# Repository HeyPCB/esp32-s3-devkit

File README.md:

# ESP32-S3 DevKit

A 31 × 64 mm ESP32-S3 development board laid out like Espressif's DevKitC-1: the WROOM-1 module at the top with its antenna on the edge, an 18-pin header down each side, three WS2812B LEDs, and USB-C between RST and BOOT.

An agent built it through [HeyPCB's MCP server](https://heypcb.ai/mcp): blocks, parts, nets, hand placement, routing and checks, all as tool calls. KiCad 10 opens the files directly, and the board is on [Circuit World](https://heypcb.ai/world/b/a0fca22e9815) to open or fork in HeyPCB (sign-in required).

## What's on it

- **ESP32-S3-WROOM-1-N8R8** (8 MB flash, 8 MB octal PSRAM). IO35–IO37 go to the PSRAM, so they are not broken out.
- **USB-C** (HRO TYPE-C-31-M-12) wired to the chip's native USB on IO19/IO20, through a **USBLC6-2SC6** ESD array, with 5.1 kΩ pull-downs on CC1 and CC2.
- **AMS1117-3.3** regulator, 5 V from USB to 3.3 V.
- **Three WS2812B LEDs** chained from IO48 through a 330 Ω resistor, powered from 5 V through a 1N5819W Schottky.
- **RST** pulls EN low and **BOOT** pulls IO0 low, with 10 kΩ pull-ups to 3.3 V and 100 nF to ground.
- **4 layers** on JLCPCB's 4-layer rules. In1 is a solid ground plane; the other three layers carry signals with ground poured around them.

Every part has an LCSC number in the BOM.

## Pinout

Headers are 2.54 mm pitch, 27.94 mm (1.1 in) between rows. Pin 1 is at the antenna end on both sides.

| Pin | Left (J2) | Right (J3) |
|---:|---|---|
| 1 | 3V3 | GND |
| 2 | EN (reset) | IO1 |
| 3 | IO4 | IO2 |
| 4 | IO5 | TXD0 |
| 5 | IO6 | RXD0 |
| 6 | IO7 | IO42 |
| 7 | IO15 | IO41 |
| 8 | IO16 | IO40 |
| 9 | IO17 | IO39 |
| 10 | IO18 | IO38 |
| 11 | IO8 | IO0 (BOOT) |
| 12 | IO3 | IO45 |
| 13 | IO46 | IO48 (LED data) |
| 14 | IO9 | IO47 |
| 15 | IO10 | IO21 |
| 16 | IO11 | IO14 |
| 17 | IO12 | IO13 |
| 18 | 5V (USB VBUS) | GND |

## Checks

Measured on this revision:

| Check | Result |
|---|---|
| DRC, HeyPCB | 0 errors, 0 unconnected |
| DRC, KiCad 10.0.6 run locally | 0 errors, 0 unconnected |
| ERC | 0 errors |
| HeyPCB verify (DRC, ERC, artwork copper, electrical rules, simulation, IR drop, physical, DFM, placement, thermal) | all 10 pass |
| Fab readiness (JLCPCB) | ready to order, 14 checks passed |

Warnings the board still carries:

- **USB pair skew is 1.45 mm against a 1.25 mm rule.** USB_DP measures 47.73 mm and USB_DN 46.28 mm. The rule comes from the USB 2.0 preset; the ESP32-S3's USB is full speed (12 Mbps). The two lines run side by side on the bottom layer, but they are not a tightly coupled pair.
- VBUS can peak at 540 mA while HeyPCB budgets 500 mA for J1, so it suggests about 290 µF more bulk capacitance near the connector.
- The regulator's input and output capacitors sit 9–10 mm from its pins: inside the limit, flagged as marginal.
- The antenna reaches free space at the top edge, but HeyPCB notes the side edges, and their ground pour, run close beside it.
- The module's ground pad has no thermal vias.
- No fiducials. J1 is a JLCPCB Extended part (a $3 feeder fee).
- A few silkscreen clearance nits.

## Files

| Path | What it is |
|---|---|
| `esp32-s3-devkit.kicad_pro`, `.kicad_sch`, `.kicad_pcb` | The KiCad 10 project |
| `heypcb-libs/` | The one footprint not in KiCad's standard library (USBLC6-2SC6, SOT-23-6), wired up by `fp-lib-table` |
| `design.json` | The HeyPCB design the schematic and board are generated from |
| `fab/` | Gerbers and drill files, BOM and pick-and-place (CPL) for JLCPCB assembly |
| `images/` | KiCad 3D renders |

## License

MIT. See [LICENSE](LICENSE).

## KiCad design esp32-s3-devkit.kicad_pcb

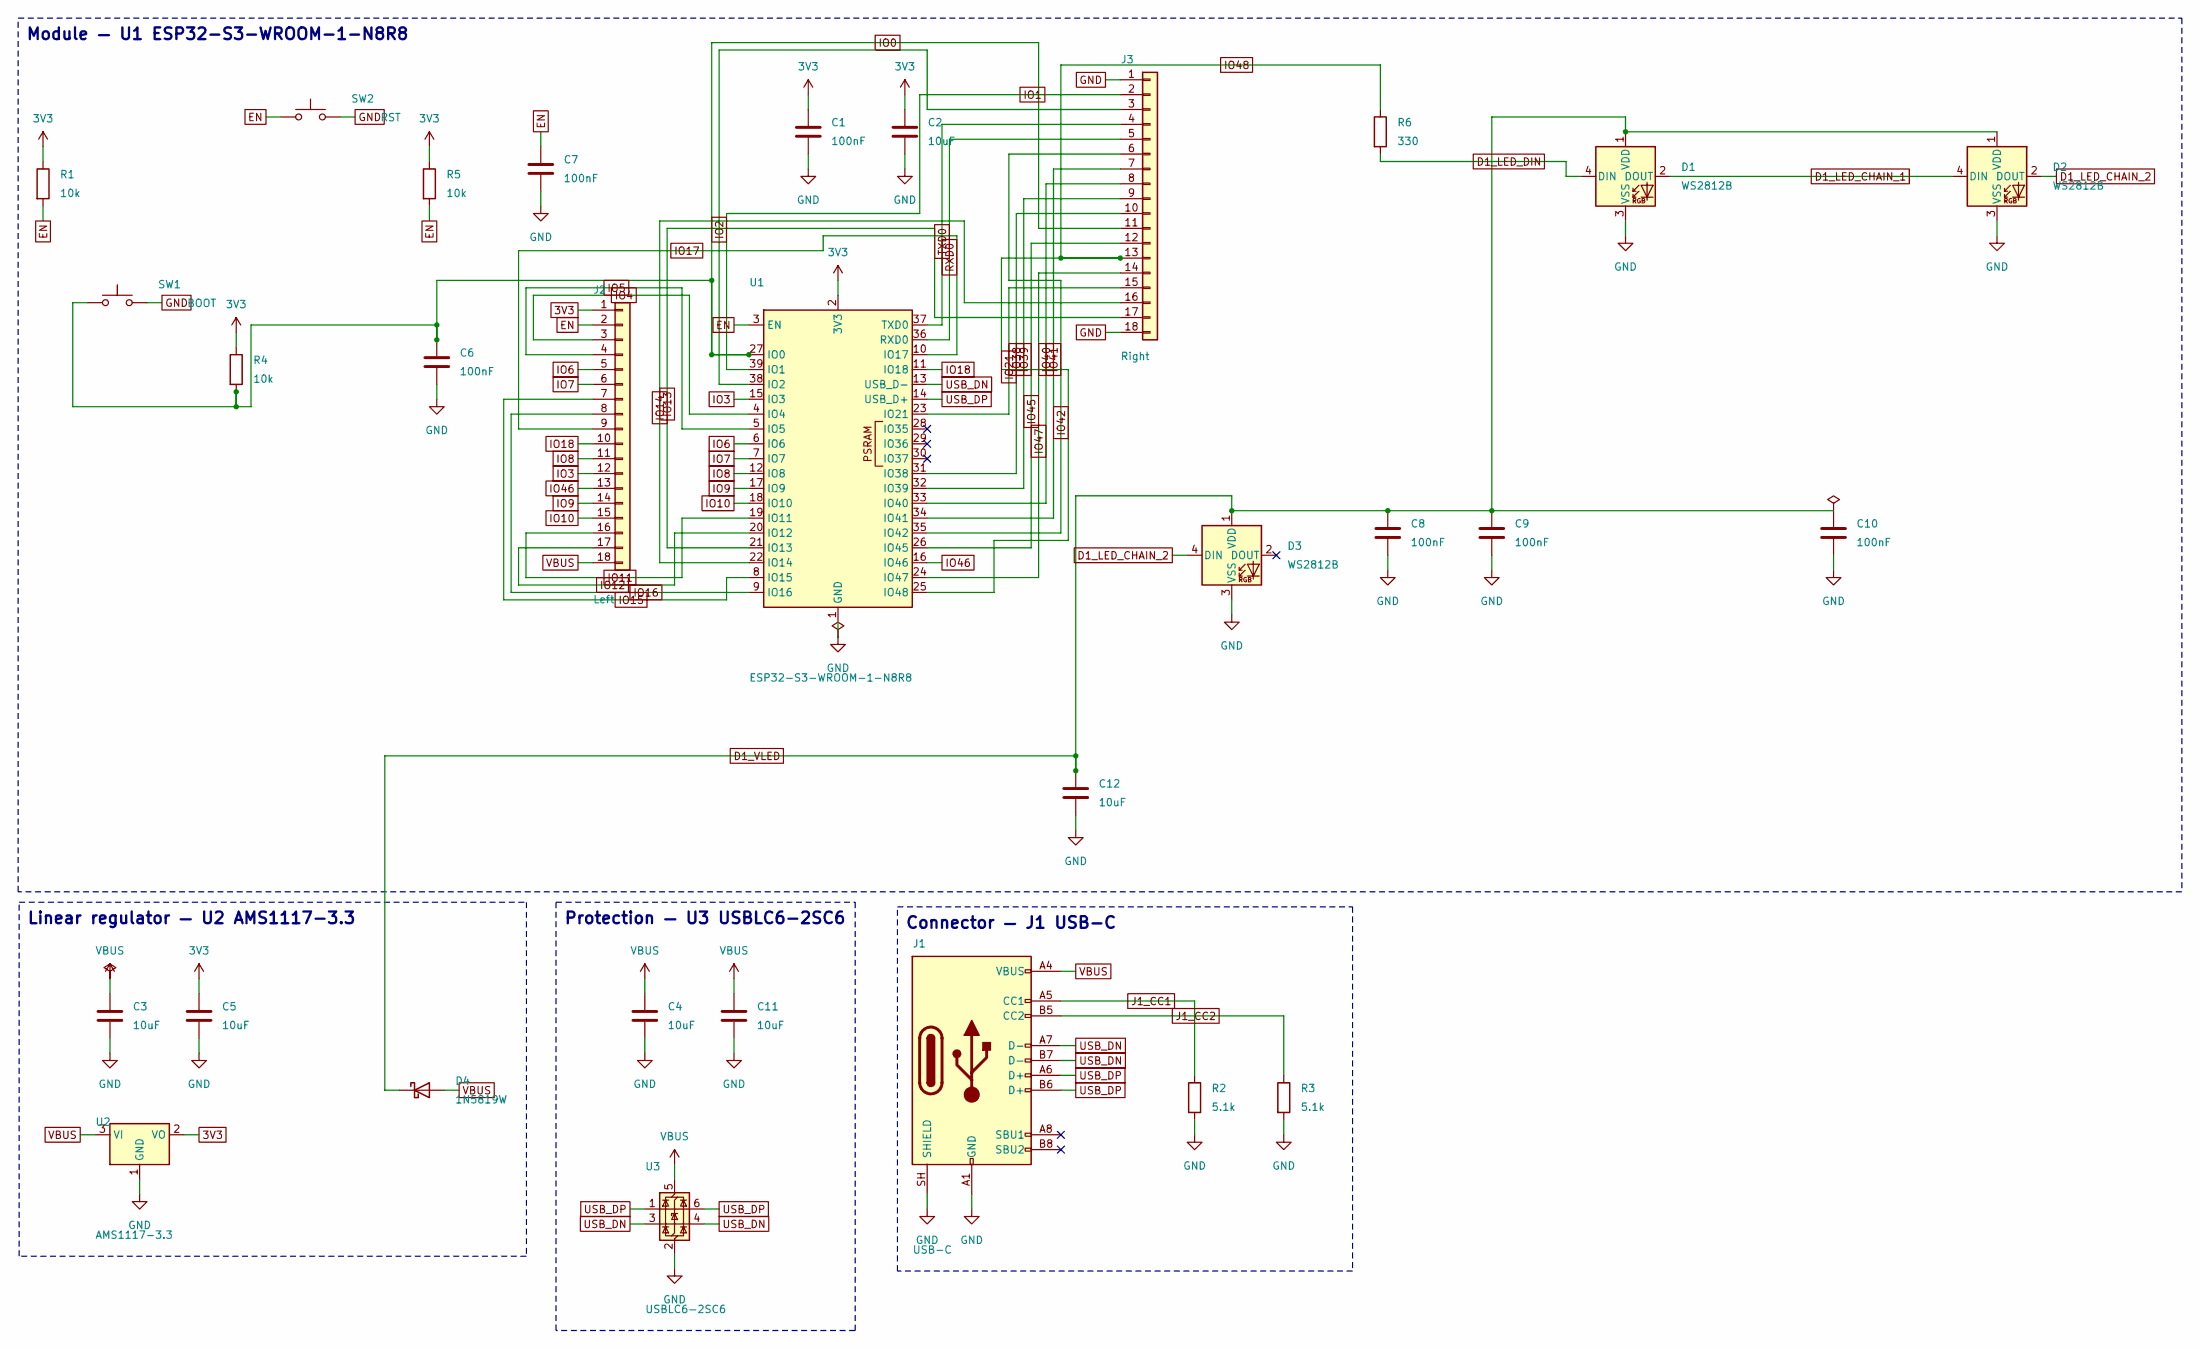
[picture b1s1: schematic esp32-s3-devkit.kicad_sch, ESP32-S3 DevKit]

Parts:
C1, C6, C7: 100nF; C_0603_1608Metric
C2, C3, C4, C5, C11, C12: 10uF; C_0805_2012Metric
C8, C9, C10: 100nF; C_0402_1005Metric
D1, D2, D3: WS2812B; LED_WS2812B_PLCC4_5.0x5.0mm_P3.2mm
D4: 1N5819W; D_SOD-123
J1: USB-C; USB_C_Receptacle_HRO_TYPE-C-31-M-12
J2: Left; PinHeader_1x18_P2.54mm_Vertical
J3: Right; PinHeader_1x18_P2.54mm_Vertical
R1, R4, R5: 10k; R_0603_1608Metric
R2, R3: 5.1k; R_0402_1005Metric
R6: 330; R_0402_1005Metric
SW1: BOOT; SW_SPST_TL3305A
SW2: RST; SW_SPST_TL3305A
U1: ESP32-S3-WROOM-1-N8R8; ESP32-S3-WROOM-1
U2: AMS1117-3.3; SOT-223-3_TabPin2
U3: USBLC6-2SC6; SOT95P280X145-6N

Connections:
3V3: C1.1, C2.1, C5.1, J2.1, R1.1, R4.1, R5.1, U1.2 (3V3), U2.2 (VO)
D1_LED_CHAIN_1: D1.2 (DOUT), D2.4 (DIN)
D1_LED_CHAIN_2: D2.2 (DOUT), D3.4 (DIN)
D1_LED_DIN: D1.4 (DIN), R6.2
D1_VLED: C8.1, C9.1, C10.1, C12.1, D1.1 (VDD), D2.1 (VDD), D3.1 (VDD), D4.1 (K)
EN: C7.1, J2.2, R1.2, R5.2, SW2.1, U1.3 (EN)
GND: C1.2, C2.2, C3.2, C4.2, C5.2, C6.2, C7.2, C8.2, C9.2, C10.2, C11.2, C12.2, D1.3 (VSS), D2.3 (VSS), D3.3 (VSS), J1.A1 (GND), J1.A12 (GND), J1.B1 (GND), J1.B12 (GND), J1.SH (SHIELD), J3.1, J3.18, R2.2, R3.2, SW1.2, SW2.2, U1.1 (GND), U1.40 (GND), U1.41 (GND), U2.1 (GND), U3.2 (GND)
IO0: C6.1, J3.11, R4.2, SW1.1, U1.27 (IO0)
IO1: J3.2, U1.39 (IO1)
IO2: J3.3, U1.38 (IO2)
IO3: J2.12, U1.15 (IO3)
IO4: J2.3, U1.4 (IO4)
IO5: J2.4, U1.5 (IO5)
IO6: J2.5, U1.6 (IO6)
IO7: J2.6, U1.7 (IO7)
IO8: J2.11, U1.12 (IO8)
IO9: J2.14, U1.17 (IO9)
IO10: J2.15, U1.18 (IO10)
IO11: J2.16, U1.19 (IO11)
IO12: J2.17, U1.20 (IO12)
IO13: J3.17, U1.21 (IO13)
IO14: J3.16, U1.22 (IO14)
IO15: J2.7, U1.8 (IO15)
IO16: J2.8, U1.9 (IO16)
IO17: J2.9, U1.10 (IO17)
IO18: J2.10, U1.11 (IO18)
IO21: J3.15, U1.23 (IO21)
IO38: J3.10, U1.31 (IO38)
IO39: J3.9, U1.32 (IO39)
IO40: J3.8, U1.33 (IO40)
IO41: J3.7, U1.34 (IO41)
IO42: J3.6, U1.35 (IO42)
IO45: J3.12, U1.26 (IO45)
IO46: J2.13, U1.16 (IO46)
IO47: J3.14, U1.24 (IO47)
IO48: J3.13, R6.1, U1.25 (IO48)
J1_CC1: J1.A5 (CC1), R2.1
J1_CC2: J1.B5 (CC2), R3.1
RXD0: J3.5, U1.36 (RXD0)
TXD0: J3.4, U1.37 (TXD0)
USB_DN: J1.A7 (D-), J1.B7 (D-), U1.13 (USB_D-), U3.3 (I/O2), U3.4 (I/O2)
USB_DP: J1.A6 (D+), J1.B6 (D+), U1.14 (USB_D+), U3.1 (I/O1), U3.6 (I/O1)
VBUS: C3.1, C4.1, C11.1, D4.2 (A), J1.A4 (VBUS), J1.A9 (VBUS), J1.B4 (VBUS), J1.B9 (VBUS), J2.18, U2.3 (VI), U3.5 (VBUS)

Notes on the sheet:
Module — U1 ESP32-S3-WROOM-1-N8R8
Linear regulator — U2 AMS1117-3.3
Protection — U3 USBLC6-2SC6
Connector — J1 USB-C

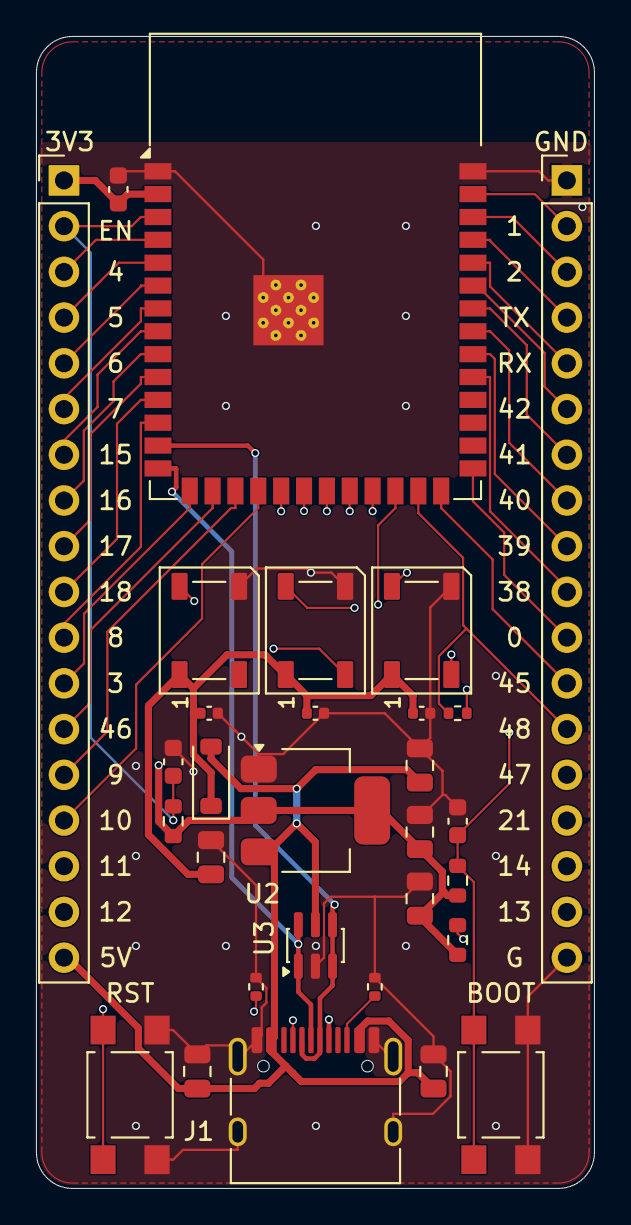
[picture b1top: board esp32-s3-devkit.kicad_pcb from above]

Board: 4 copper layers, 31.0 x 64.0 mm, 30 parts (0 on the bottom side), 43 nets.

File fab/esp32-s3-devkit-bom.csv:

Comment,Designator,Footprint,LCSC Part #
100nF,"C1,C6,C7",C_0603_1608Metric,C14663
10uF,"C2,C3,C4,C5,C11,C12",C_0805_2012Metric,C15850
100nF,"C8,C9,C10",C_0402_1005Metric,C1525
WS2812B,"D1,D2,D3",LED_WS2812B_PLCC4_5.0x5.0mm_P3.2mm,C2761795
1N5819W,D4,D_SOD-123,C369937
USB-C,J1,USB_C_Receptacle_HRO_TYPE-C-31-M-12,C165948
Left,J2,PinHeader_1x18_P2.54mm_Vertical,C2894941
Right,J3,PinHeader_1x18_P2.54mm_Vertical,C2894941
10k,"R1,R4,R5",R_0603_1608Metric,C25804
5.1k,"R2,R3",R_0402_1005Metric,C25905
330,R6,R_0402_1005Metric,C25104
BOOT,SW1,SW_SPST_TL3305A,C2886902
RST,SW2,SW_SPST_TL3305A,C2886902
ESP32-S3-WROOM-1-N8R8,U1,ESP32-S3-WROOM-1,C2913201
AMS1117-3.3,U2,SOT-223-3_TabPin2,C6186
USBLC6-2SC6,U3,SOT95P280X145-6N,C2827654
